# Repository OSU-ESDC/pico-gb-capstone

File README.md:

# Gaming System - A Modified RP2040 GB for the ENGR 512 Capstone group at Oregon State University

This is a fork of the [RP2040-GB Game Boy (DMG) emulator by YouMakeTech, originally forked from Deltabeard's version](https://github.com/YouMakeTech/Pico-GB). RP2040-GB is a Game Boy (DMG) emulator Peanut-GB on the Raspberry Pi RP2040 microcontroller, using an ILI9225 screen. Runs at more than 70 fps without audio emulation. With frame skip and interlacing, can run at up to 120 fps.

This fork includes changes done by me for my Capstone project in Winter/Spring 2025:
* Volume control via rotary encoder support
* Game movement via analog joystick support
* I2C communication with ADC support, enabling the analog joystick to be used

The Gaming System has a 3D printed shell, designed by Justin Gonzalez. You can find the stl files for the print in the print folder. 

# Videos
* [Analog Joystick Functionality](https://www.youtube.com/shorts/wKSmv8ernYQ)
* [Case Dissasembly](https://www.youtube.com/shorts/b-UEHgNEkO8)
* [Volume Knob Functionality](https://www.youtube.com/shorts/HMfL2WKNLts)

# Hardware
## What you need
* (1x) [Raspberry Pi Pico](https://amzn.to/3rAcmDy)
* (1x) [ADS7830 8-bit, 8-channel, I2C ADC](https://www.adafruit.com/product/5836)
* (1x) [Rotary Encoder](https://eecs.engineering.oregonstate.edu/education/tekbotSuite/tekbot/pages/publicInventoryPart.php?stocknumber=KIJRQN)
* (1x) [Analog Joystick](https://eecs.engineering.oregonstate.edu/education/tekbotSuite/tekbot/pages/publicInventoryPart.php?stocknumber=S5GS9V)
* (1x) [2.2inch ILI9225 176×220 LCD Display Module](https://amzn.to/3aNAMD7)
* (1x) [FAT 32 formatted Micro SD card + adapter](https://amzn.to/3ICKzcm) with roms you legally own. Roms must have the .gb extension and must be copied to the root folder.
* (1x) [MAX98357A amplifier](https://www.youmaketech.com/max98357)
* (1x) [2W 8ohms speaker](https://amzn.to/3ikDy6S)
* (8x) [Micro Push Button Switch, Momentary Tactile Tact Touch, 6x6x6 mm, 4 pins](https://amzn.to/3dyXBsx)
* (1x) [Solderable Breadboard](https://amzn.to/3lwvfDi)
* [Dupont Wires Assorted Kit (Male to Female + Male to Male + Female to Female)](https://amzn.to/3HtbvdO)
* [Preformed Breadboard Jumper Wires](https://amzn.to/3rxwVjM)

## Setting up the hardware
#### Most of the setup is here, minus the analog joystick/rotary encoder:
[Pico-GB assembly instructions, circuit diagrams, 3d printed files etc.](https://www.youmaketech.com/pico-gb-gameboy-emulator-handheld-for-raspberry-pi-pico/)
You can find the rest of the setup in the documentation in the /docs folder.  

# Pinout
* I2C SDA = GP0
* I2C SCL = GP1
* UP = GP2
* DOWN = GP3
* LEFT = GP4
* RIGHT = GP5
* BUTTON A = GP6
* BUTTON B = GP7
* SELECT = GP8
* START = GP9
* VOLUME DT = GP10
* VOLUME CLK = GP11
* SD MISO = GP12
* SD CS = GP13
* SD CSK = GP14
* SD MOSI = GP15
* VOLUME MUTE = GP16
* LCD CS = GP17
* LCD CLK = GP18
* LCD SDI = GP19
* LCD RS = GP20
* LCD RST = GP21
* LCD LED = GP22
* MAX98357A DIN = GP26
* MAX98357A BCLK = GP27
* MAX98357A LRC = GP28

# Flashing the firmware
* Download RP2040_GB.uf2 from the [releases page](https://github.com/osu-esdc/pico-gb-capstone/releases)
* Push and hold the BOOTSEL button on the Pico, then connect to your computer using a micro USB cable. Release BOOTSEL once the drive RPI-RP2 appears on your computer.
* Drag and drop the UF2 file on to the RPI-RP2 drive. The Raspberry Pi Pico will reboot and will now run the emulator.

# Preparing the SD card
The SD card is used to store game roms and save game progress. For this project, you will need a FAT 32 formatted Micro SD card with roms you legally own. Roms must have the .gb extension.

* Insert your SD card in a Windows computer and format it as FAT 32
* Copy your .gb files to the SD card root folder (subfolders are not supported at this time)
* Insert the SD card into the ILI9225 SD card slot using a Micro SD adapter

# Building from source
The [Raspberry Pi Pico SDK](https://github.com/raspberrypi/pico-sdk) is required to build this project. 
To start, clone the SDK in a known folder (labeled as path-to-sdk in future commands), update CMake and submodules, and export the pico sdk path:
```
git clone git@github.com:raspberrypi/pico-sdk.git
cd pico-sdk
git submodule update --init
sudo apt install cmake python3 build-essential gcc-arm-none-eabi libnewlib-arm-none-eabi libstdc++-arm-none-eabi-newlib 
export PICO_SDK_PATH=<path-to-sdk>/pico-sdk
cd ..
```
Clone this repository and create a build folder:
```
git clone git@github.com:osu-esdc/pico-gb-capstone.git
cd pico-gb-capstone
mkdir build
cd build
```

Build a Makefile for the project (no debugging):
```
cmake ..
```

Create the executable and program the Pico:
```
make
sudo openocd -f interface/cmsis-dap.cfg -f target/rp2040.cfg -c "adapter speed 5000" -c "program RP2040_GB.elf verify reset exit"
```

#### For debugging using a Pico Tool (using gdb server and client):
Build a Makefile for the project (with debugging):
```
cmake .. -DCMAKE_BUILD_TYPE=Debug
```
Run the following in one window:
```
sudo openocd -f interface/cmsis-dap.cfg -f target/rp2040.cfg -c "adapter speed 5000"
```
Then run this in the other window:
```
arm-none-eabi-gdb
(gdb) start_pico
```
For tips on setting up debugging tools, follow the [Arm GNU Toolchain setup guide](https://github.com/osu-esdc/Arm-GNU-Toolchain-Setup)

# Known issues and limitations
* No copyrighted games are included with Pico-GB / RP2040-GB. For this project, you will need a FAT 32 formatted Micro SD card with roms you legally own. Roms must have the .gb extension.
* The RP2040-GB emulator is able to run at full speed on the Pico, at the expense of emulation accuracy. Some games may not work as expected or may not work at all. RP2040-GB is still experimental and not all features are guaranteed to work.
* RP2040-GB is only compatible with [original Game Boy DMG games](https://en.wikipedia.org/wiki/List_of_Game_Boy_games) (not compatible with Game Boy Color or Game Boy Advance games)
* Repeatedly flashing your Pico will eventually wear out the flash memory (Pico is qualified for min. 100K flash/erase cycles)
* The emulator overclocks the Pico in order to get the emulator working fast enough. Overclocking can reduce the Pico’s lifespan.
* Use this software and instructions at your own risk! I will not be responsible in any way for any damage to your Pico and/or connected peripherals caused by using this software. I also do not take responsibility in any way when damage is caused to the Pico or display due to incorrect wiring or voltages.

# License
MIT

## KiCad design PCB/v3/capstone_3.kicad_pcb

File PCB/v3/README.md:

### This folder contains all the folders and files necessary to edit and manufacture the Gaming System's PCB.
#### Folders: 
- The gerber files folder contains all of the gerber files required to get the PCB manufactured. You can ignore the "Capstone_1-bottom" and "Capstone_1-top" files.
- The myLibrary.pretty folder contains additional footprints for the PCB.

#### Files (within this directory): 
- There are 3 important files in this directory:  
        capstone_3.kicad_pro - project file to edit files  
        capstone_3.kicad_pcb - board layout file  
        capstone_3.kicad_sch - schematic file

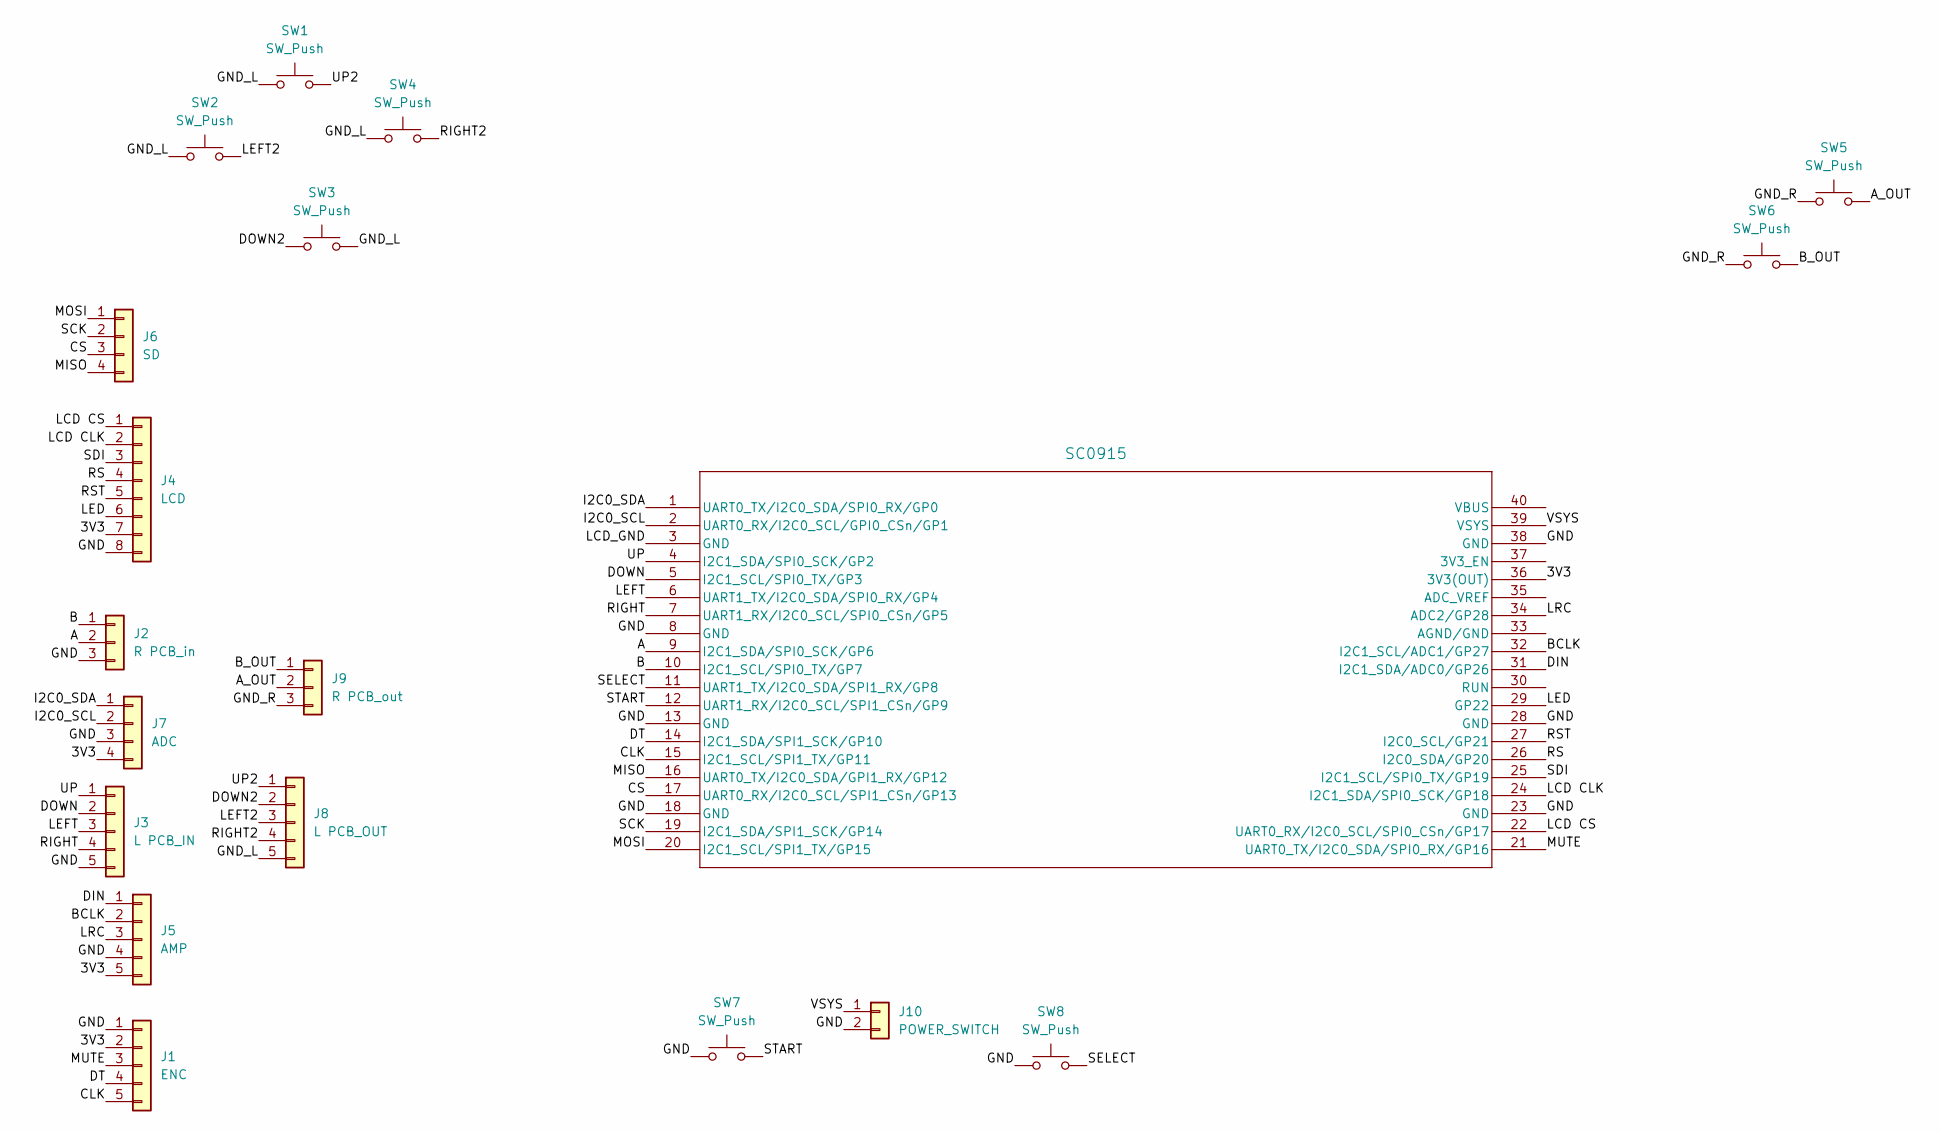
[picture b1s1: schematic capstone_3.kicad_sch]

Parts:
J1: ENC; PinHeader_1x05_P1.27mm_Vertical
J2: R PCB_in; PinHeader_1x03_P1.27mm_Vertical
J3: L PCB_IN; PinHeader_1x05_P1.27mm_Vertical
J4: LCD; PinHeader_1x08_P1.27mm_Vertical
J5: AMP; PinHeader_1x05_P1.27mm_Vertical
J6: SD; PinHeader_1x04_P1.27mm_Vertical
J7: ADC; PinHeader_1x04_P1.27mm_Vertical
J8: L PCB_OUT; PinHeader_1x05_P1.27mm_Vertical
J9: R PCB_out; PinHeader_1x03_P1.27mm_Vertical
J10: POWER_SWITCH; PinHeader_1x02_P2.54mm_Vertical
SW1, SW2, SW3, SW4, SW5, SW6, SW7, SW8: SW_Push; SW_PUSH_6mm
U2: SC0915; Pico THT

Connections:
/3V3: J1.2, J4.7, J5.5, J7.4, U2.36 (3V3(OUT))
/A: J2.2, U2.9 (I2C1_SDA/SPI0_SCK/GP6)
/A_OUT: J9.2, SW5.2
/B: J2.1, U2.10 (I2C1_SCL/SPI0_TX/GP7)
/BCLK: J5.2, U2.32 (I2C1_SCL/ADC1/GP27)
/B_OUT: J9.1, SW6.2
/CLK: J1.5, U2.15 (I2C1_SCL/SPI1_TX/GP11)
/CS: J6.3, U2.17 (UART0_RX/I2C0_SCL/SPI1_CSn/GP13)
/DIN: J5.1, U2.31 (I2C1_SDA/ADC0/GP26)
/DOWN: J3.2, U2.5 (I2C1_SCL/SPI0_TX/GP3)
/DOWN2: J8.2, SW3.1
/DT: J1.4, U2.14 (I2C1_SDA/SPI1_SCK/GP10)
/GND: J1.1, J2.3, J3.5, J4.8, J5.4, J7.3, J10.2, SW7.1, SW8.1, U2.8 (GND), U2.13 (GND), U2.18 (GND), U2.23 (GND), U2.28 (GND), U2.38 (GND)
/GND_L: J8.5, SW1.1, SW2.1, SW3.2, SW4.1
/GND_R: J9.3, SW5.1, SW6.1
/I2C0_SCL: J7.2, U2.2 (UART0_RX/I2C0_SCL/GPI0_CSn/GP1)
/I2C0_SDA: J7.1, U2.1 (UART0_TX/I2C0_SDA/SPI0_RX/GP0)
/LCD CLK: J4.2, U2.24 (I2C1_SDA/SPI0_SCK/GP18)
/LCD CS: J4.1, U2.22 (UART0_RX/I2C0_SCL/SPI0_CSn/GP17)
/LCD_GND: U2.3 (GND)
/LED: J4.6, U2.29 (GP22)
/LEFT: J3.3, U2.6 (UART1_TX/I2C0_SDA/SPI0_RX/GP4)
/LEFT2: J8.3, SW2.2
/LRC: J5.3, U2.34 (ADC2/GP28)
/MISO: J6.4, U2.16 (UART0_TX/I2C0_SDA/GPI1_RX/GP12)
/MOSI: J6.1, U2.20 (I2C1_SCL/SPI1_TX/GP15)
/MUTE: J1.3, U2.21 (UART0_TX/I2C0_SDA/SPI0_RX/GP16)
/RIGHT: J3.4, U2.7 (UART1_RX/I2C0_SCL/SPI0_CSn/GP5)
/RIGHT2: J8.4, SW4.2
/RS: J4.4, U2.26 (I2C0_SDA/GP20)
/RST: J4.5, U2.27 (I2C0_SCL/GP21)
/SCK: J6.2, U2.19 (I2C1_SDA/SPI1_SCK/GP14)
/SDI: J4.3, U2.25 (I2C1_SCL/SPI0_TX/GP19)
/SELECT: SW8.2, U2.11 (UART1_TX/I2C0_SDA/SPI1_RX/GP8)
/START: SW7.2, U2.12 (UART1_RX/I2C0_SCL/SPI1_CSn/GP9)
/UP: J3.1, U2.4 (I2C1_SDA/SPI0_SCK/GP2)
/UP2: J8.1, SW1.2
/VSYS: J10.1, U2.39 (VSYS)

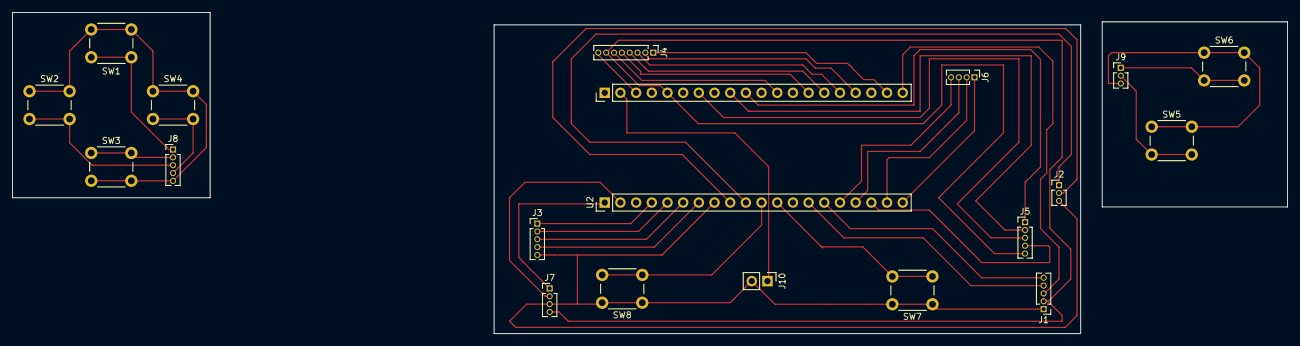
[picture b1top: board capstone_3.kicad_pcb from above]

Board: 2 copper layers, 206.5 x 52.0 mm, 19 parts (0 on the bottom side), 37 nets.

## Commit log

2025-03-03 created build directory; did some other stuff - starting on getting the code to run on the RP2040.
2025-03-19 added functionality to toggle on-board LED.
2025-03-20 started rotary encoder stuff
2025-04-08 starting adding I2C stuff
2025-04-09 continuing the i2c grind
2025-04-24 working version
2025-05-01 got left movement working on the joystick.
2025-05-01 got analog joystick working perfectly
2025-06-02 working copy
2025-06-02 working, cleaned up version
2025-06-02 working both versions - with and without rotary encoder/analog joystick
2025-06-02 cleaned up more
2025-06-02 removing stuff
2025-06-04 Create test
2025-06-04 Rename ENGR 512 TEAM Final Report.pdf to Capstone Final Report.pdf
2025-06-05 changed a comment
2025-06-07 Rename Capstone Electronic Block Diagram.drawio to Capstone Electronics Block Diagram.drawio
2025-06-07 Create t
2025-06-07 Rename README.md to README.md
2025-06-07 still need to add pcb
